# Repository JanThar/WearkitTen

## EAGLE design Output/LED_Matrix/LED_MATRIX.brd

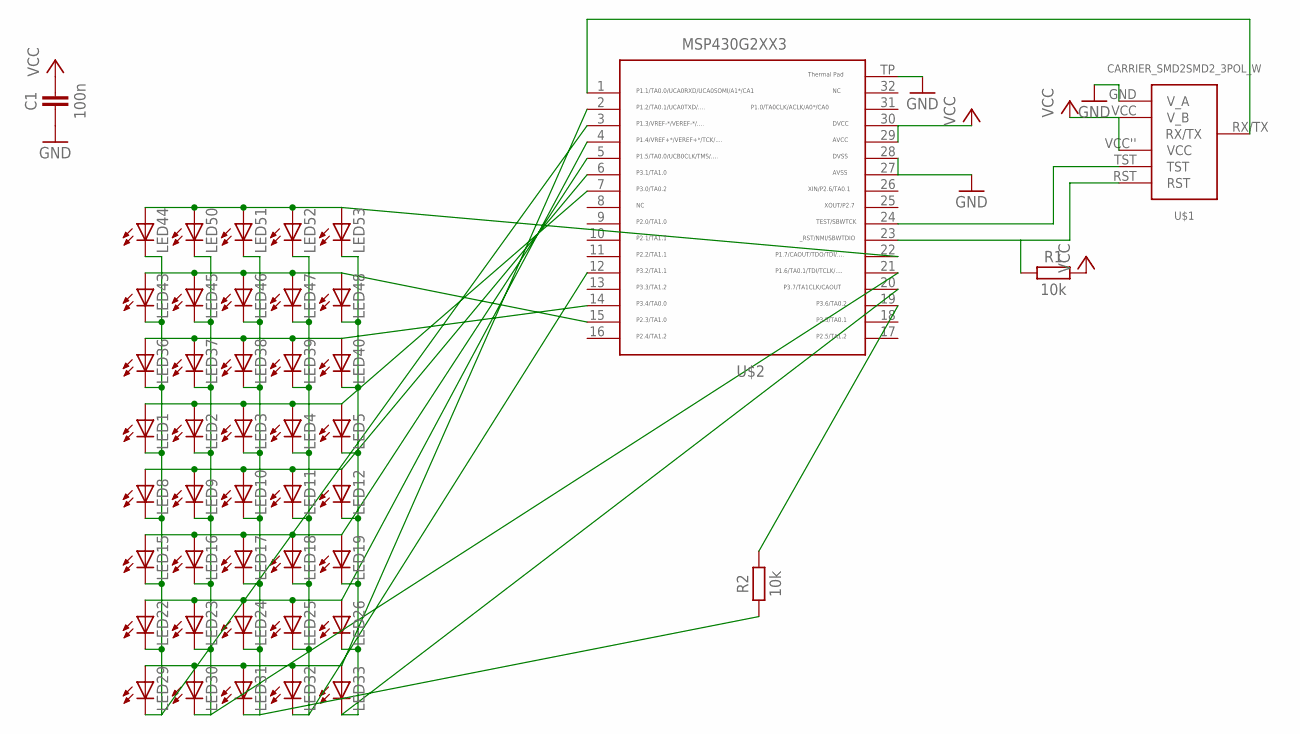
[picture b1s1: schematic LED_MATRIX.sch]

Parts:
C1: 100n; 603
LED1, LED2, LED3, LED4, LED5, LED8, LED9, LED10, LED11, LED12, LED15, LED16, LED17, LED18, LED19, LED22, LED23, LED24, LED25, LED26, LED29, LED30, LED31, LED32, LED33, LED36, LED37, LED38, LED39, LED40, LED43, LED44, LED45, LED46, LED47, LED48, LED50, LED51, LED52, LED53: LEDCHIPLED_0603; CHIPLED_0603
R1: 10k; 603
R2: 10k; 603_SMALL
U$1: CARRIER_SMD2SMD2_3POL_W; CARRIER_SMD2_WIDE_3POL
U$2: MSP430G2553; QFN32

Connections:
GND: C1.1, U$1.GND (V_A), U$2.27, U$2.28, U$2.TP
unnamed: U$1.TST, U$2.24
unnamed: R1.1, U$1.RST, U$2.23
unnamed: U$1.RX/TX, U$2.1
unnamed: LED36.A, LED37.A, LED38.A, LED39.A, LED40.A, U$2.14
unnamed: LED44.A, LED50.A, LED51.A, LED52.A, LED53.A, U$2.22
unnamed: LED43.A, LED45.A, LED46.A, LED47.A, LED48.A, U$2.15
unnamed: R2.2, U$2.19
unnamed: LED1.A, LED2.A, LED3.A, LED4.A, LED5.A, U$2.7
unnamed: LED8.A, LED9.A, LED10.A, LED11.A, LED12.A, U$2.6
unnamed: LED15.A, LED16.A, LED17.A, LED18.A, LED19.A, U$2.5
unnamed: LED22.A, LED23.A, LED24.A, LED25.A, LED26.A, U$2.4
unnamed: LED29.A, LED30.A, LED31.A, LED32.A, LED33.A, U$2.2
unnamed: LED1.C, LED8.C, LED15.C, LED22.C, LED29.C, LED36.C, LED43.C, LED44.C, U$2.3
unnamed: LED2.C, LED9.C, LED16.C, LED23.C, LED30.C, LED37.C, LED45.C, LED50.C, U$2.21
unnamed: LED3.C, LED10.C, LED17.C, LED24.C, LED31.C, LED38.C, LED46.C, LED51.C, R2.1
unnamed: LED4.C, LED11.C, LED18.C, LED25.C, LED32.C, LED39.C, LED47.C, LED52.C, U$2.12
unnamed: LED5.C, LED12.C, LED19.C, LED26.C, LED33.C, LED40.C, LED48.C, LED53.C, U$2.20
VCC: C1.2, R1.2, U$1.VCC (V_B), U$1.VCC'' (VCC), U$2.29, U$2.30

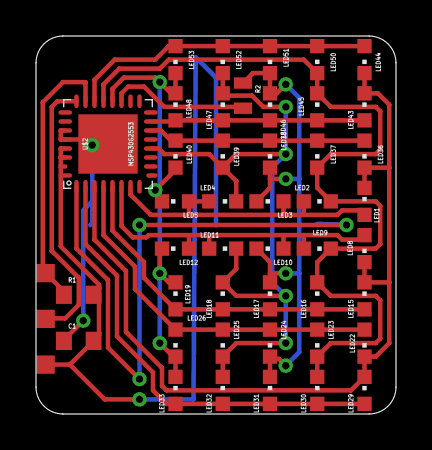
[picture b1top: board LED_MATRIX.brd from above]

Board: 2 copper layers, 20.0 x 21.0 mm, 45 parts (0 on the bottom side), 19 nets.

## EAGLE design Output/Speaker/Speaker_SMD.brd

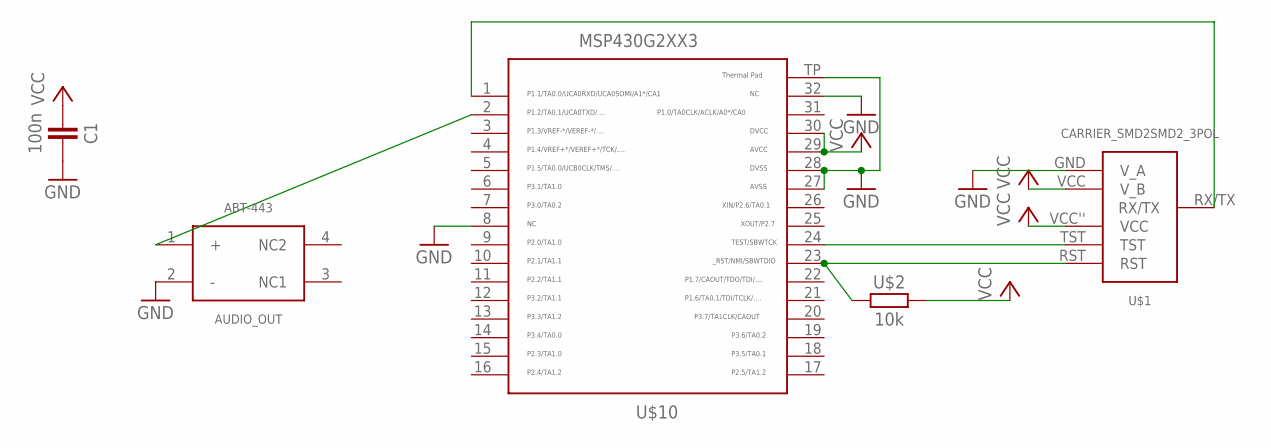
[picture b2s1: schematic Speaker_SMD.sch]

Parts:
AUDIO_OUT: ABT-443; ABT-443-RC
C1: 100n; 603
U$1: CARRIER_SMD2SMD2_3POL; CARRIER_SMD2_3POL
U$2: 10k; 603
U$10: MSP430G2553; QFN32

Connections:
GND: AUDIO_OUT.2 (-), C1.2, U$1.GND (V_A), U$10.8, U$10.27, U$10.28, U$10.32, U$10.TP
unnamed: AUDIO_OUT.1 (+), U$10.2
unnamed: U$1.TST, U$10.24
unnamed: U$1.RST, U$2.1, U$10.23
unnamed: U$1.RX/TX, U$10.1
VCC: C1.1, U$1.VCC (V_B), U$1.VCC'' (VCC), U$2.2, U$10.29, U$10.30

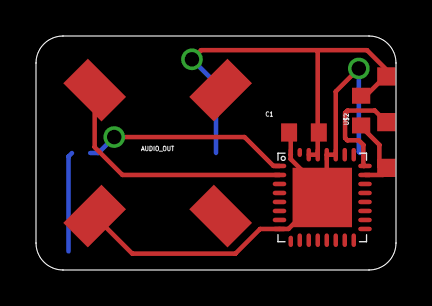
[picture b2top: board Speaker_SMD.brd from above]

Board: 2 copper layers, 20.0 x 13.0 mm, 5 parts (0 on the bottom side), 6 nets.

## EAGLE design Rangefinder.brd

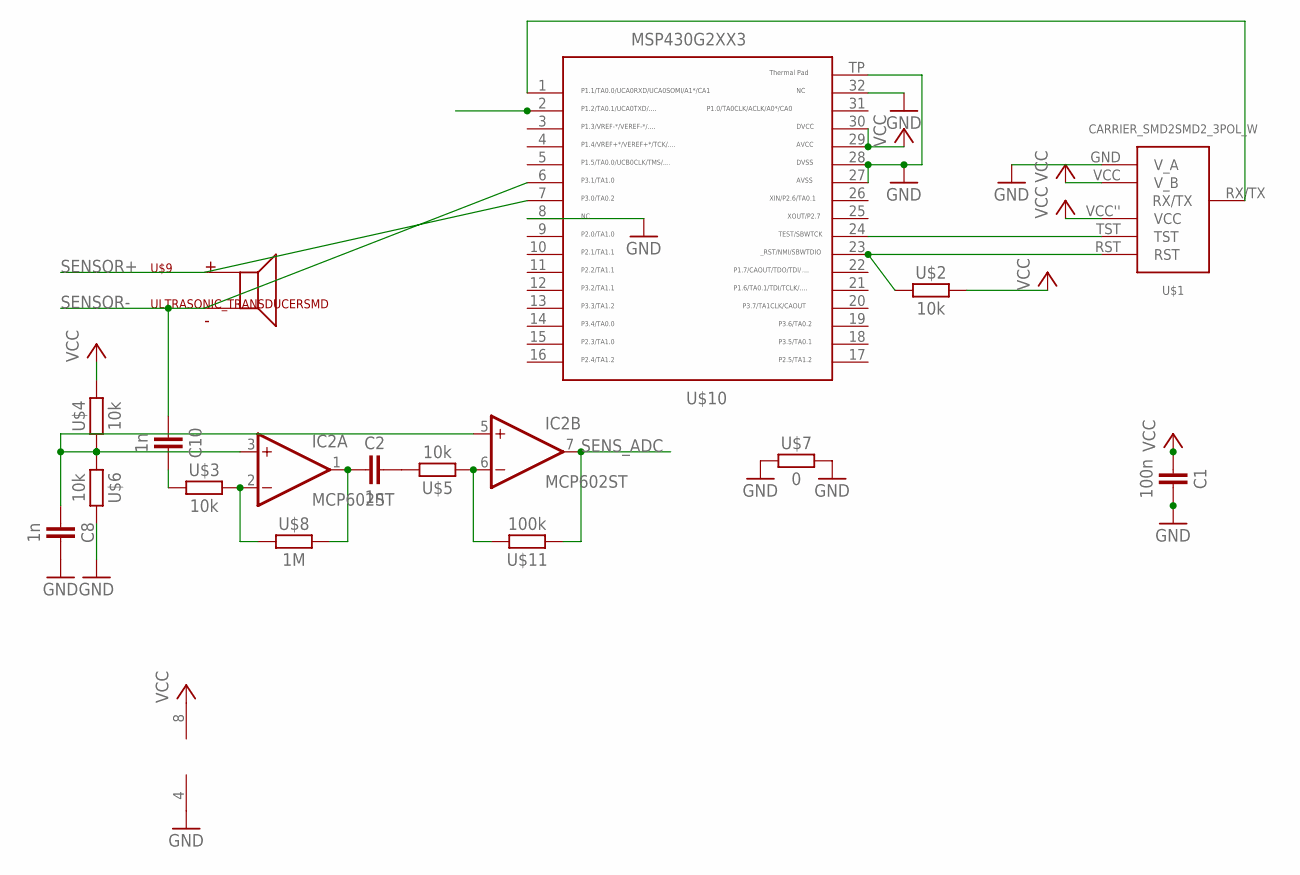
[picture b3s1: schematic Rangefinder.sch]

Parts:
C1: 100n; 603
C2, C8, C10: 1n; 603
IC2: MCP602ST; TSSOP8
U$1: CARRIER_SMD2SMD2_3POL_W; CARRIER_SMD2_WIDE_3POL
U$2, U$3, U$4, U$5, U$6: 10k; 603
U$7: 0; 603
U$8: 1M; 603
U$9: ULTRASONIC_TRANSDUCERSMD; TRANSDUCER2
U$10: MSP430G2553; QFN32
U$11: 100k; 603

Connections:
GND: C1.2, C8.2, IC2.4 (V-), U$1.GND (V_A), U$6.2, U$7.1, U$7.2, U$10.8, U$10.27, U$10.28, U$10.32, U$10.TP
unnamed: C10.2, U$3.1
unnamed: U$1.TST, U$10.24
unnamed: U$1.RST, U$2.1, U$10.23
unnamed: C2.2, U$5.2
unnamed: IC2.6 (-IN), U$5.1, U$11.2
unnamed: U$1.RX/TX, U$10.1
unnamed: C8.1, IC2.3 (+IN), IC2.5 (+IN), U$4.1, U$6.1
unnamed: IC2.2 (-IN), U$3.2, U$8.1
unnamed: C2.1, IC2.1 (OUT), U$8.2
SENSOR+: U$9.P$3, U$10.7
SENSOR-: C10.1, U$9.P$4, U$10.6
SENS_ADC: IC2.7 (OUT), U$10.2, U$11.1
VCC: C1.1, IC2.8 (V+), U$1.VCC (V_B), U$1.VCC'' (VCC), U$2.2, U$4.2, U$10.29, U$10.30

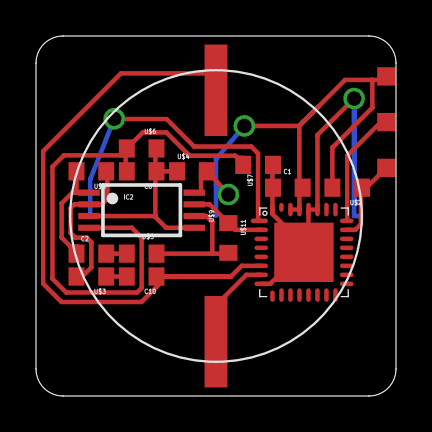
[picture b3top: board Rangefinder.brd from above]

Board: 2 copper layers, 20.0 x 20.0 mm, 16 parts (0 on the bottom side), 14 nets.
